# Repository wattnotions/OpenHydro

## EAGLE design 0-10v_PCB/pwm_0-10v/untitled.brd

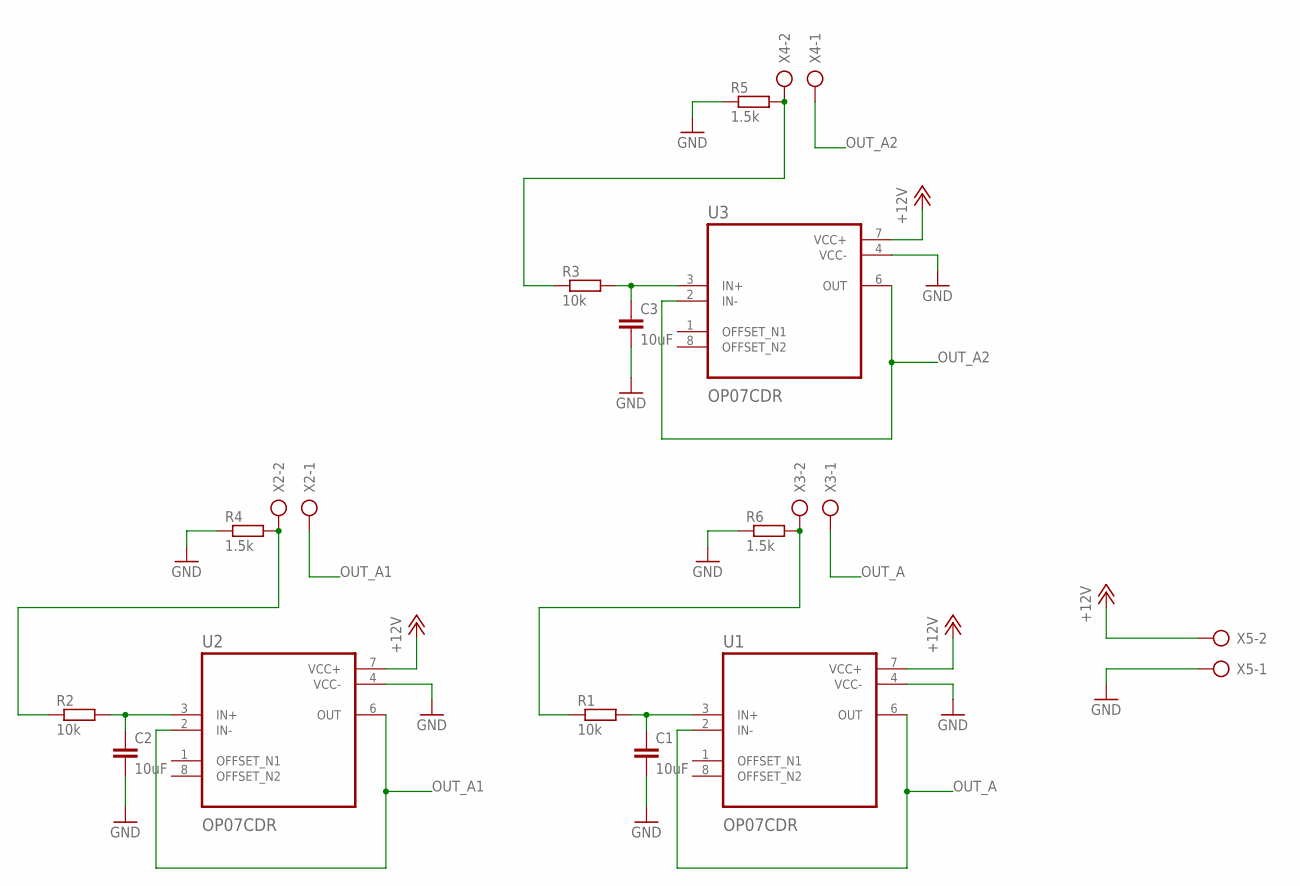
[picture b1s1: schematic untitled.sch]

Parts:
C1, C2, C3: 10uF; C0805
R1, R2, R3: 10k; M0805
R4, R5, R6: 1.5k; M0805
U1, U2, U3: OP07CDR; SOIC127P599X175-8N
X2, X3, X4, X5: AK500/2

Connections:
+12V: U1.7 (VCC+), U2.7 (VCC+), U3.7 (VCC+), X5.2
GND: C1.2, C2.2, C3.2, R4.1, R5.1, R6.1, U1.4 (VCC-), U2.4 (VCC-), U3.4 (VCC-), X5.1
unnamed: R1.1, R6.2, X3.2
unnamed: C1.1, R1.2, U1.3 (IN+)
unnamed: R2.1, R4.2, X2.2
unnamed: C2.1, R2.2, U2.3 (IN+)
unnamed: R3.1, R5.2, X4.2
unnamed: C3.1, R3.2, U3.3 (IN+)
OUT_A: U1.2 (IN-), U1.6 (OUT), X3.1
OUT_A1: U2.2 (IN-), U2.6 (OUT), X2.1
OUT_A2: U3.2 (IN-), U3.6 (OUT), X4.1

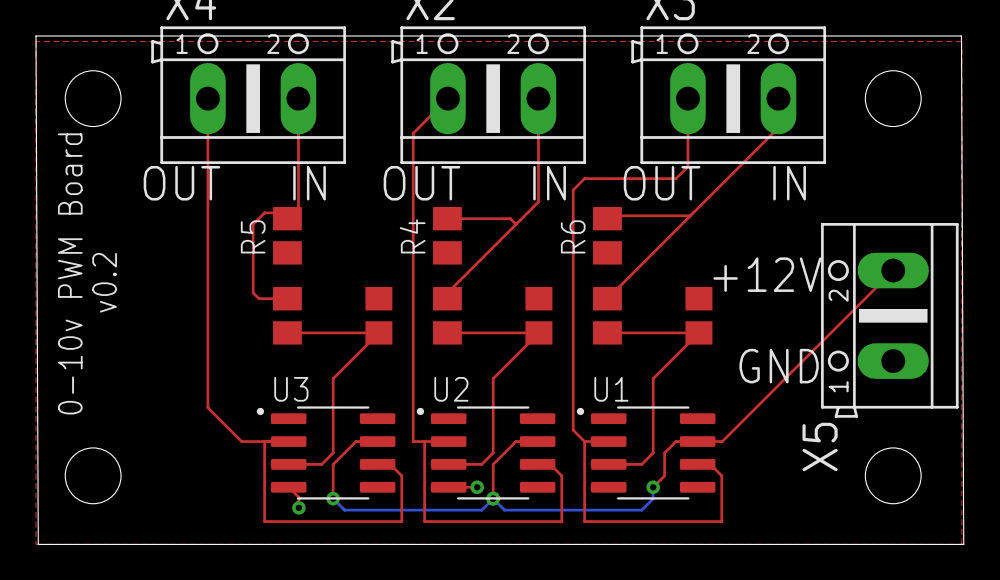
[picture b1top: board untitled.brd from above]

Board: 2 copper layers, 51.5 x 28.2 mm, 16 parts (0 on the bottom side), 11 nets.

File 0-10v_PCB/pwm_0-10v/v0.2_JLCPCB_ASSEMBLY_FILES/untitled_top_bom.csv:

Comment,Designator,Footprint,LCSC Part #
1.5k,R4 R5 R6,M0805,
10k,R1 R2 R3,M0805,
10uF,C1 C2 C3,C0805,
OP07CDR,U1 U2 U3,SOIC127P599X175-8N,

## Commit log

2020-08-29 Changed folder structure
2020-08-30 mqtt dht11 test example working
2020-08-30 created kicad project
2020-08-30 changed ip to domain
2020-08-30 almost working - publish response needed
2020-09-01 added arduino uno schematic
2020-09-01 removed 3.3v reg and changed to 4 pin conn input
2020-09-01 added usb circuitry
2020-09-01 added modbus connectors
2020-09-01 changed 12v input to global label
2020-09-01 added 3.3v regulator
2020-09-02 changed rs485 transceiver to sp485e
2020-09-02 changed dir structure
2020-09-02 added datasheet
2020-09-02 started bme280 wiring
2020-09-03 added sensair s8
2020-09-03 added level shift app note
2020-09-03 added level shifter for bme280
2020-09-03 changed bme280 to use i2c
2020-09-03 ADDED BREAKOUT PINS
2020-09-04 schematic finished
2020-09-04 assign footprints 80% completed
2020-09-05 routing started 15%
2020-09-06 routing 50%
2020-09-06 routing 60% completed
2020-09-06 started placing mounting holes
2020-09-06 edge cuts layer with mounting holes complete
2020-09-06 routing complete
2020-09-07 made 12v bus line bigger and moved away from bme280
2020-09-07 added missing dtr trace
2020-09-07 moved vin trace away from bme280
2020-09-07 fixed senseair s8 pin mixup - added lots of silk text
2020-09-08 changed board outline to rectangle
2020-09-14 working publish example
2020-09-14 added json print just to see formatting
2020-09-20 rpc receive almost fully working
2020-09-21 progressed rpc response, not quite there
2020-09-21 fixed incorrect atmega328p pinout
2020-09-21 cleaned up drc violations
2020-09-21 removed 2nd connector - fixed mounting holes
2020-09-23 generated files for jlcpcb fab
2020-09-23 rpc mqtt receive and ack working
2020-10-03 bme280 comms working
2020-10-03 added senseair s8 library
2020-10-03 working s8 example
2020-10-03 silkscreen cleanup
2020-10-03 added s8 modbus/uart datasheet
2020-10-17 working softserial modbus example
2020-10-17 modbus read mqtt send basic example working!!
    need to look at main loop, not written correctly from mqtt pov need client.loop() in there somewhere
2020-10-17 added bme280 code with modbus code....working
2020-10-24 got temp float formatting working
2020-10-24 temp, humidity and pressure mqtt send working
2020-10-24 fixed main loop - more mqtt keepalive friendly
2020-10-24 dir rename
2020-10-24 dashboard save addded
2020-10-24 added comments
2020-10-25 added c02 code and extra comments
2020-10-25 c02 modbus read working
2020-10-25 co2 modbus read from slave working
2020-10-25 started design spec document
2020-11-01 added img upload scripts
2020-11-01 updated design spec
2020-11-03 added crontab with thingboard service restart
2020-11-07 more descriptive file name
2020-12-12 made eagle project
2020-12-12 added ltspice files
2020-12-12 dir restructure
2020-12-12 added sensor node case 3d print files
2020-12-12 added analog circuitry
2020-12-12 made .brd file
2020-12-13 part placement completed
2020-12-19 made centroid file
2020-12-19 added external tab for bme280 ic
2020-12-19 moved bme280 to tab
2020-12-19 added tab to gnd fill zone
2020-12-19 put curved edges on tab
2020-12-19 replaced missing gnd plane
2020-12-19 fixed max485 wiring issues on schematic
2020-12-19 routed max485 en to ard d8
2020-12-19 added sht20 to tab
2020-12-20 added dps310 to schem and board
2020-12-20 changed term block to 5.08mm - added silk pin labels
2020-12-20 changed usb ic to cp2102 on schematic
2020-12-20 cp2102 routing complete
2020-12-20 added status led to pin 25
2020-12-20 made term block silk invisible
2020-12-20 changed cp2102 to 28 pin version
2020-12-20 generated fab files
2020-12-30 changed screw terminals to correct size
2020-12-30 kicad files
2020-12-30 added silk screen text
2020-12-30 added 1.5k pull down resistor to all inputs
2020-12-30 added board name + version to silk text
2020-12-30 made board a bit bigger
2020-12-30 fixed silk text wrong layer
2020-12-30 fixed another silk issue- generated gerbers for v0.2
2020-12-30 changed pulldown resistors to 1.5k instead of 10k
2021-03-06 got JSON parse working
2021-03-06 made json parse add on func
2021-03-06 fixed bug with SP update func
2021-03-06 fixed typo
2021-03-08 fixed bug with temp SP knob update
2021-04-11 works but have slave select bug occurs
2021-05-03 reverted to a previous working commit
2021-05-03 changed slave address to 5
2021-05-03 added slave address print from mem addr 5
2021-05-03 address printing from slaves is working
    can now tell the two slaves apart
2021-05-03 added save sensor values in local variables
2021-05-03 basic on off control implemented - untested
